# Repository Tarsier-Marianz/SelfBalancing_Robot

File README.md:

# SelfBalancing_Robot-KiCAD

Prototype board for self balancing robot.

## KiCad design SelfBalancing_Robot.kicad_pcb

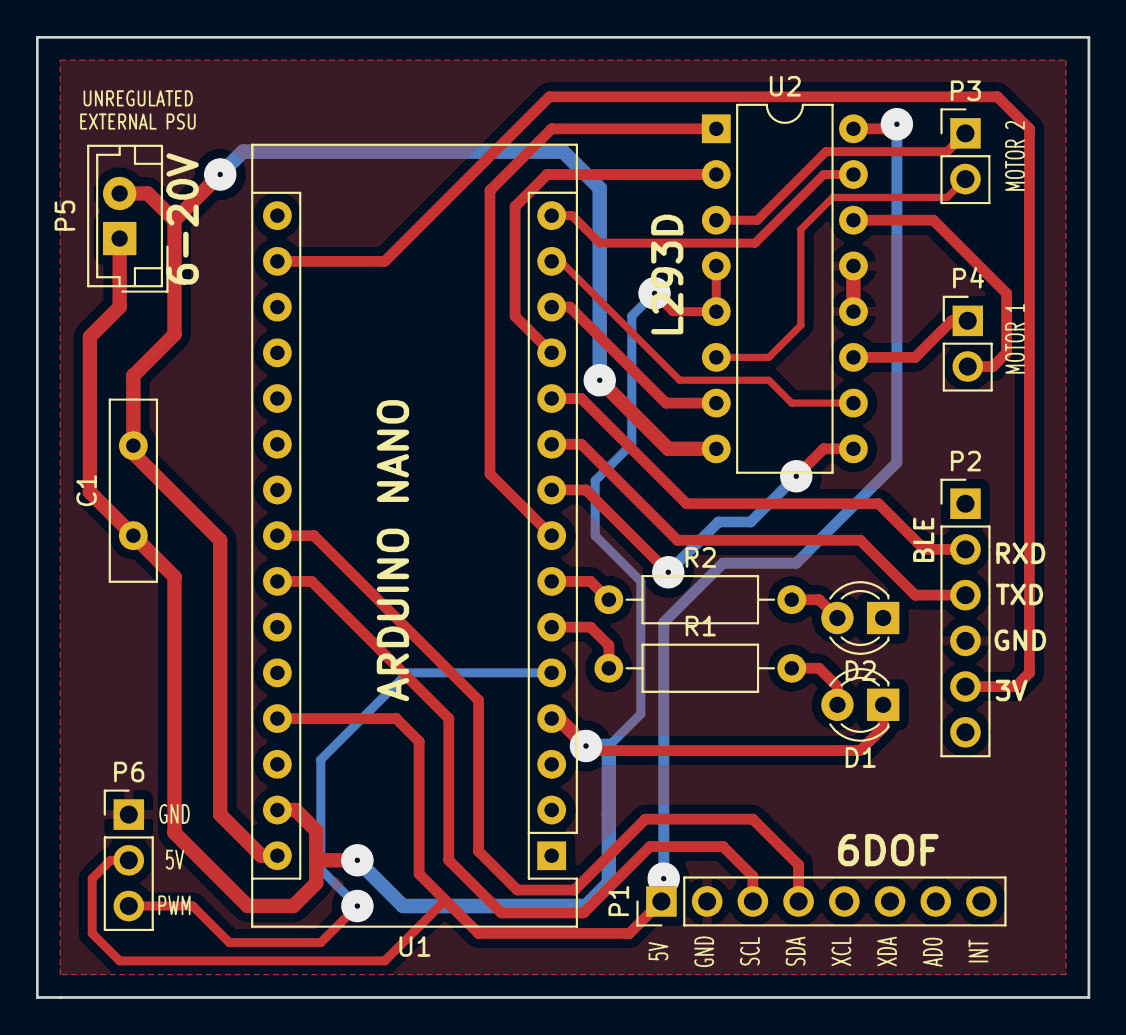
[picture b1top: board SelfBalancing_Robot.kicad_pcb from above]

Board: 2 copper layers, 58.4 x 53.3 mm, 13 parts (0 on the bottom side), 24 nets.

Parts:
C1: C_Small; C_Disc_D10.0mm_W2.5mm_P5.00mm
D1, D2: LED; LED_D3.0mm
P1: CONN_01X08; Pin_Header_Straight_1x08_Pitch2.54mm
P2: CONN_01X06; Pin_Header_Straight_1x06_Pitch2.54mm
P3, P4: CONN_01X02; Pin_Header_Straight_1x02_Pitch2.54mm
P5: CONN_01X02; JST_EH_B02B-EH-A_02x2.50mm_Straight
P6: CONN_01X03; Pin_Header_Straight_1x03_Pitch2.54mm
R1, R2: R; R_Axial_DIN0207_L6.3mm_D2.5mm_P10.16mm_Horizontal
U1: ArduinoNano; Arduino_Nano
U2: L293D; DIP-16_W7.62mm

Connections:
/3V3: P2.5, U1.17
/5V: P1.1, P6.2, U1.27, U2.16
/9V: C1.2, P5.2, U1.30, U2.8
/EN1: U1.8, U2.1
/EN2: U1.9, U2.9
/GND: P1.2, P2.4, P6.1, U2.12, U2.13
/IN1: U1.12, U2.2
/IN2: U1.13, U2.7
/IN3: U1.14, U2.10
/IN4: U1.15, U2.15
/OUT1: P3.1, U2.3
/OUT2: P3.2, U2.6
/OUT3: P4.1, U2.11
/OUT4: P4.2, U2.14
/PWM: P6.3, U1.5
/RXD: P2.2, U1.11
/SCL: P1.3, U1.24
/SDA: P1.4, U1.23
/TXD: P2.3, U1.10
unnamed: C1.1, D1.1, D2.1, P5.1, U1.4, U1.29, U2.4, U2.5
unnamed: D1.2, R1.2
unnamed: D2.2, R2.2
unnamed: R1.1, U1.6
unnamed: R2.1, U1.7

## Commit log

2018-10-27 +LED indicator resistors
2018-10-27 +servo output connector
2018-10-27 +servo connector pcb footprint
2018-10-27 *labels in silk
2018-10-27 *readme content
2018-10-31 +adding capacitors to L293D
